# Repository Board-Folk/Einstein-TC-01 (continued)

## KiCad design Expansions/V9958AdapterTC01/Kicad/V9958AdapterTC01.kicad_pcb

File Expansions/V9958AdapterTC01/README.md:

# Einstein TC-01 V9958/V9938 VDP adapter

Adapter board to allow the use of a Yamaha V9958 or V9938 VDP chip on the Tatung Einstein TC-01. The board requires 192KB RAM, as 6 of 4464 (41464) RAM chips, to make the video capability of the board same as (or better than) the Einstein 256, and works with the ROM from that machine, e.g. XTAL MOS 2.1.

The board plugs into the existing VDP socket, replacing the original TMS VDP chip, and connects to video output by replacing the jumpers at M100/101 outputting RGB to the socket on the back of the TC-01. This disconnects the other video circuitry and RF output on the main board, that being YUV based.

The VDP plug to get the right height has been tested with 2 of 20 pin 15mm single pin headers and for connection for video output, 2x08 PC104 pin plug with a single spacer. Careful, as big pins can bork a DIP-40 socket, so be prepared to change that if necessary. Holes for nylon standoffs have been included at the other end of the board for support, though this isn't really necessary.

Address line A1 needs connecting up for this to function as it's not present on the original VDP socket. This is the pin with a box on the two pin header on the edge of this board. The nearest point on the main board for buffered A1 is pin 3 of I28.

Video output is provided by simple transistor based circuits. It seems fine, but some resistor values may need tweaking.

You do not need to fit the video RAM chips on the main board at I40 and I41 with this installed.

Not used or tested at the moment is the other pin on the header next to A1 which is for /WAIT which may or may not be used by any software at all, don't know about this, so connected this with a diode D151 (flagged DNP) between the VDP and the pin header. There isn't anything on the main board that uses /WAIT - that only connects to the Tatung Tube expansion port. This doesn't need connecting unless software uses it, and isn't required to function generally.

Note: The pre-connected solder bridge on the bottom of the board - required for the V9958 - should be cut if installing a V9938. This has now been tested and works fine.

Some fake/relabelled AliExpress RAM got very hot and died on this board after passing regular RAM tests, so be careful what you use. Not sure of the official speed requirements. Equally, there are plenty of completely fake V9958, many labelled copyright 1901.

## Update

A couple of issues have been noted when installing this on an original factory built TC-01 that didn't crop up in testing on the replica build. The first relating to this board, the second relating to the use of the Einstein 256 ROM in the TC-01.

### Fix 1

The original voltage regulator at I106 as factory fitted is a LM350T5, which with this VDP adapter fitted overheats and cuts out causing the system to crash. This needs replacing with a higher rating compatible regulator, 1 Amp or greater. Fitting the wrong voltage regulator or voltage regulator the wrong way round will cause serious damage. This has been successfully tested with a Traco TSR 1-2450. You can test the voltage either side of C057 (C57 on the replica) before fitting any VDP for 5V.

### Fix 2

On some systems with the Einstein 256 ROM fitted, Alph lock randomly enables and disables. This is due to a port being missing at address 26h that is present on the Einstein 256 and not on the TC-01. A patch to the ROM is needed to stop this happening.

Port 26h is read and checked for bit 0 for the Alph key being pressed in 3 places in the ROM code, first offset 7d8h. The three occurrences of db26e601 can be replaced with with db26e600 - removing the bit comparison for the Alph key.

## Photos

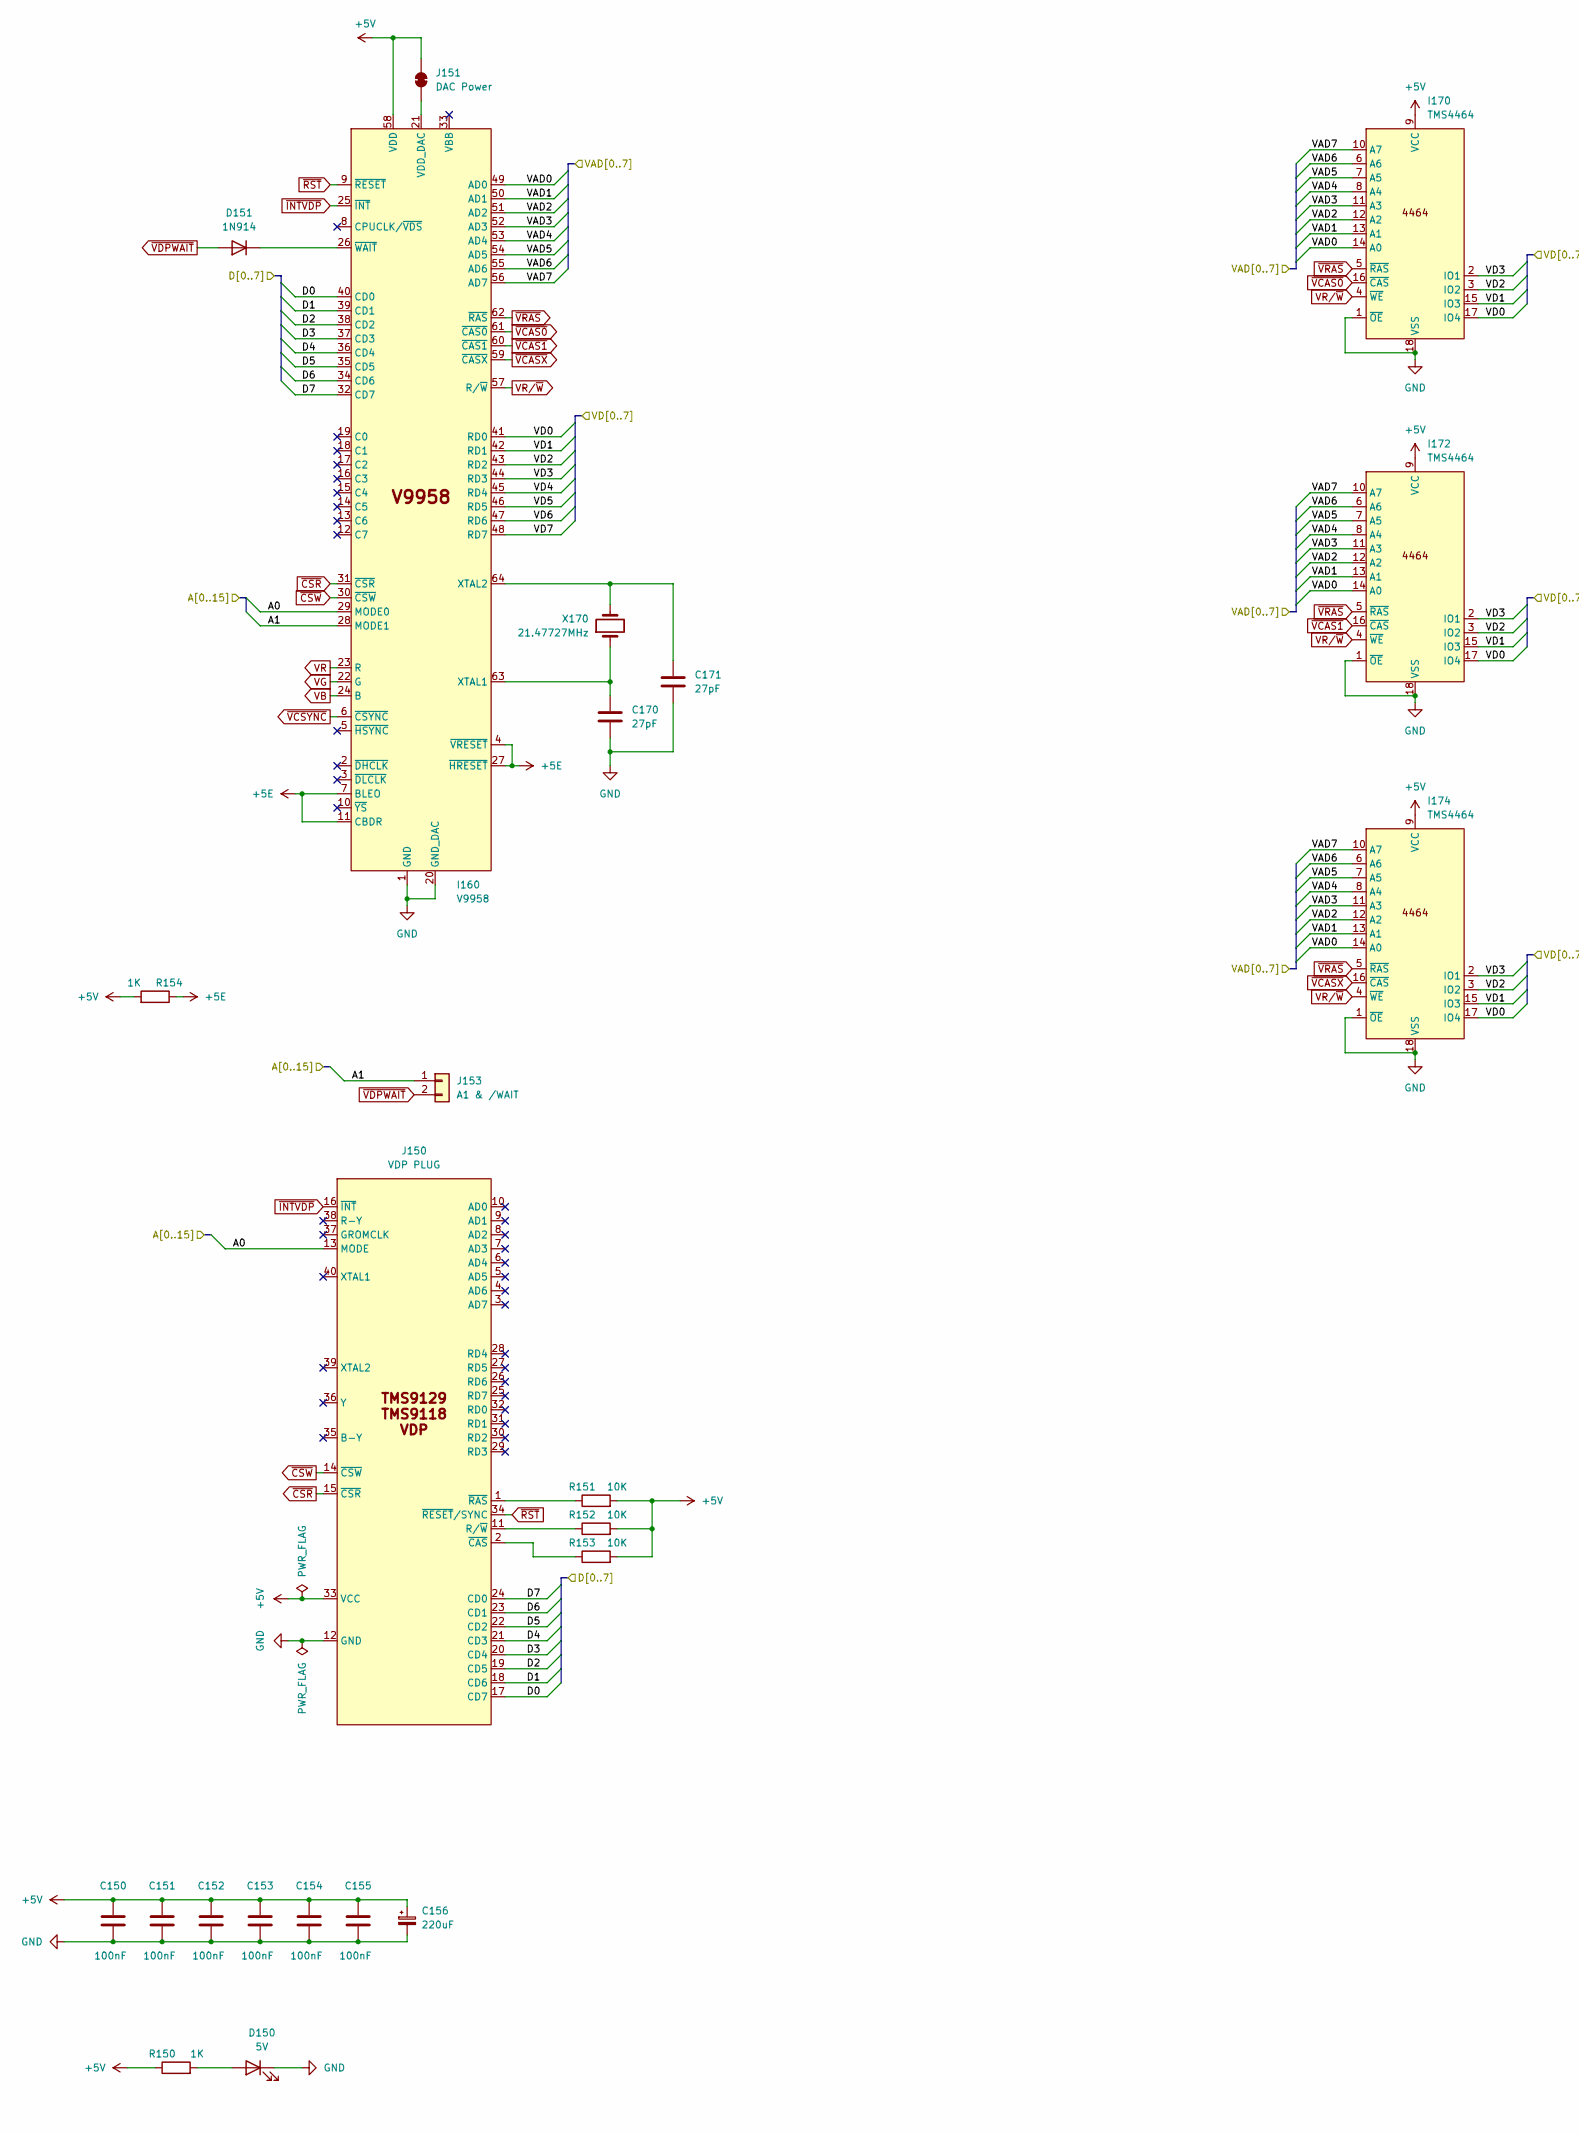
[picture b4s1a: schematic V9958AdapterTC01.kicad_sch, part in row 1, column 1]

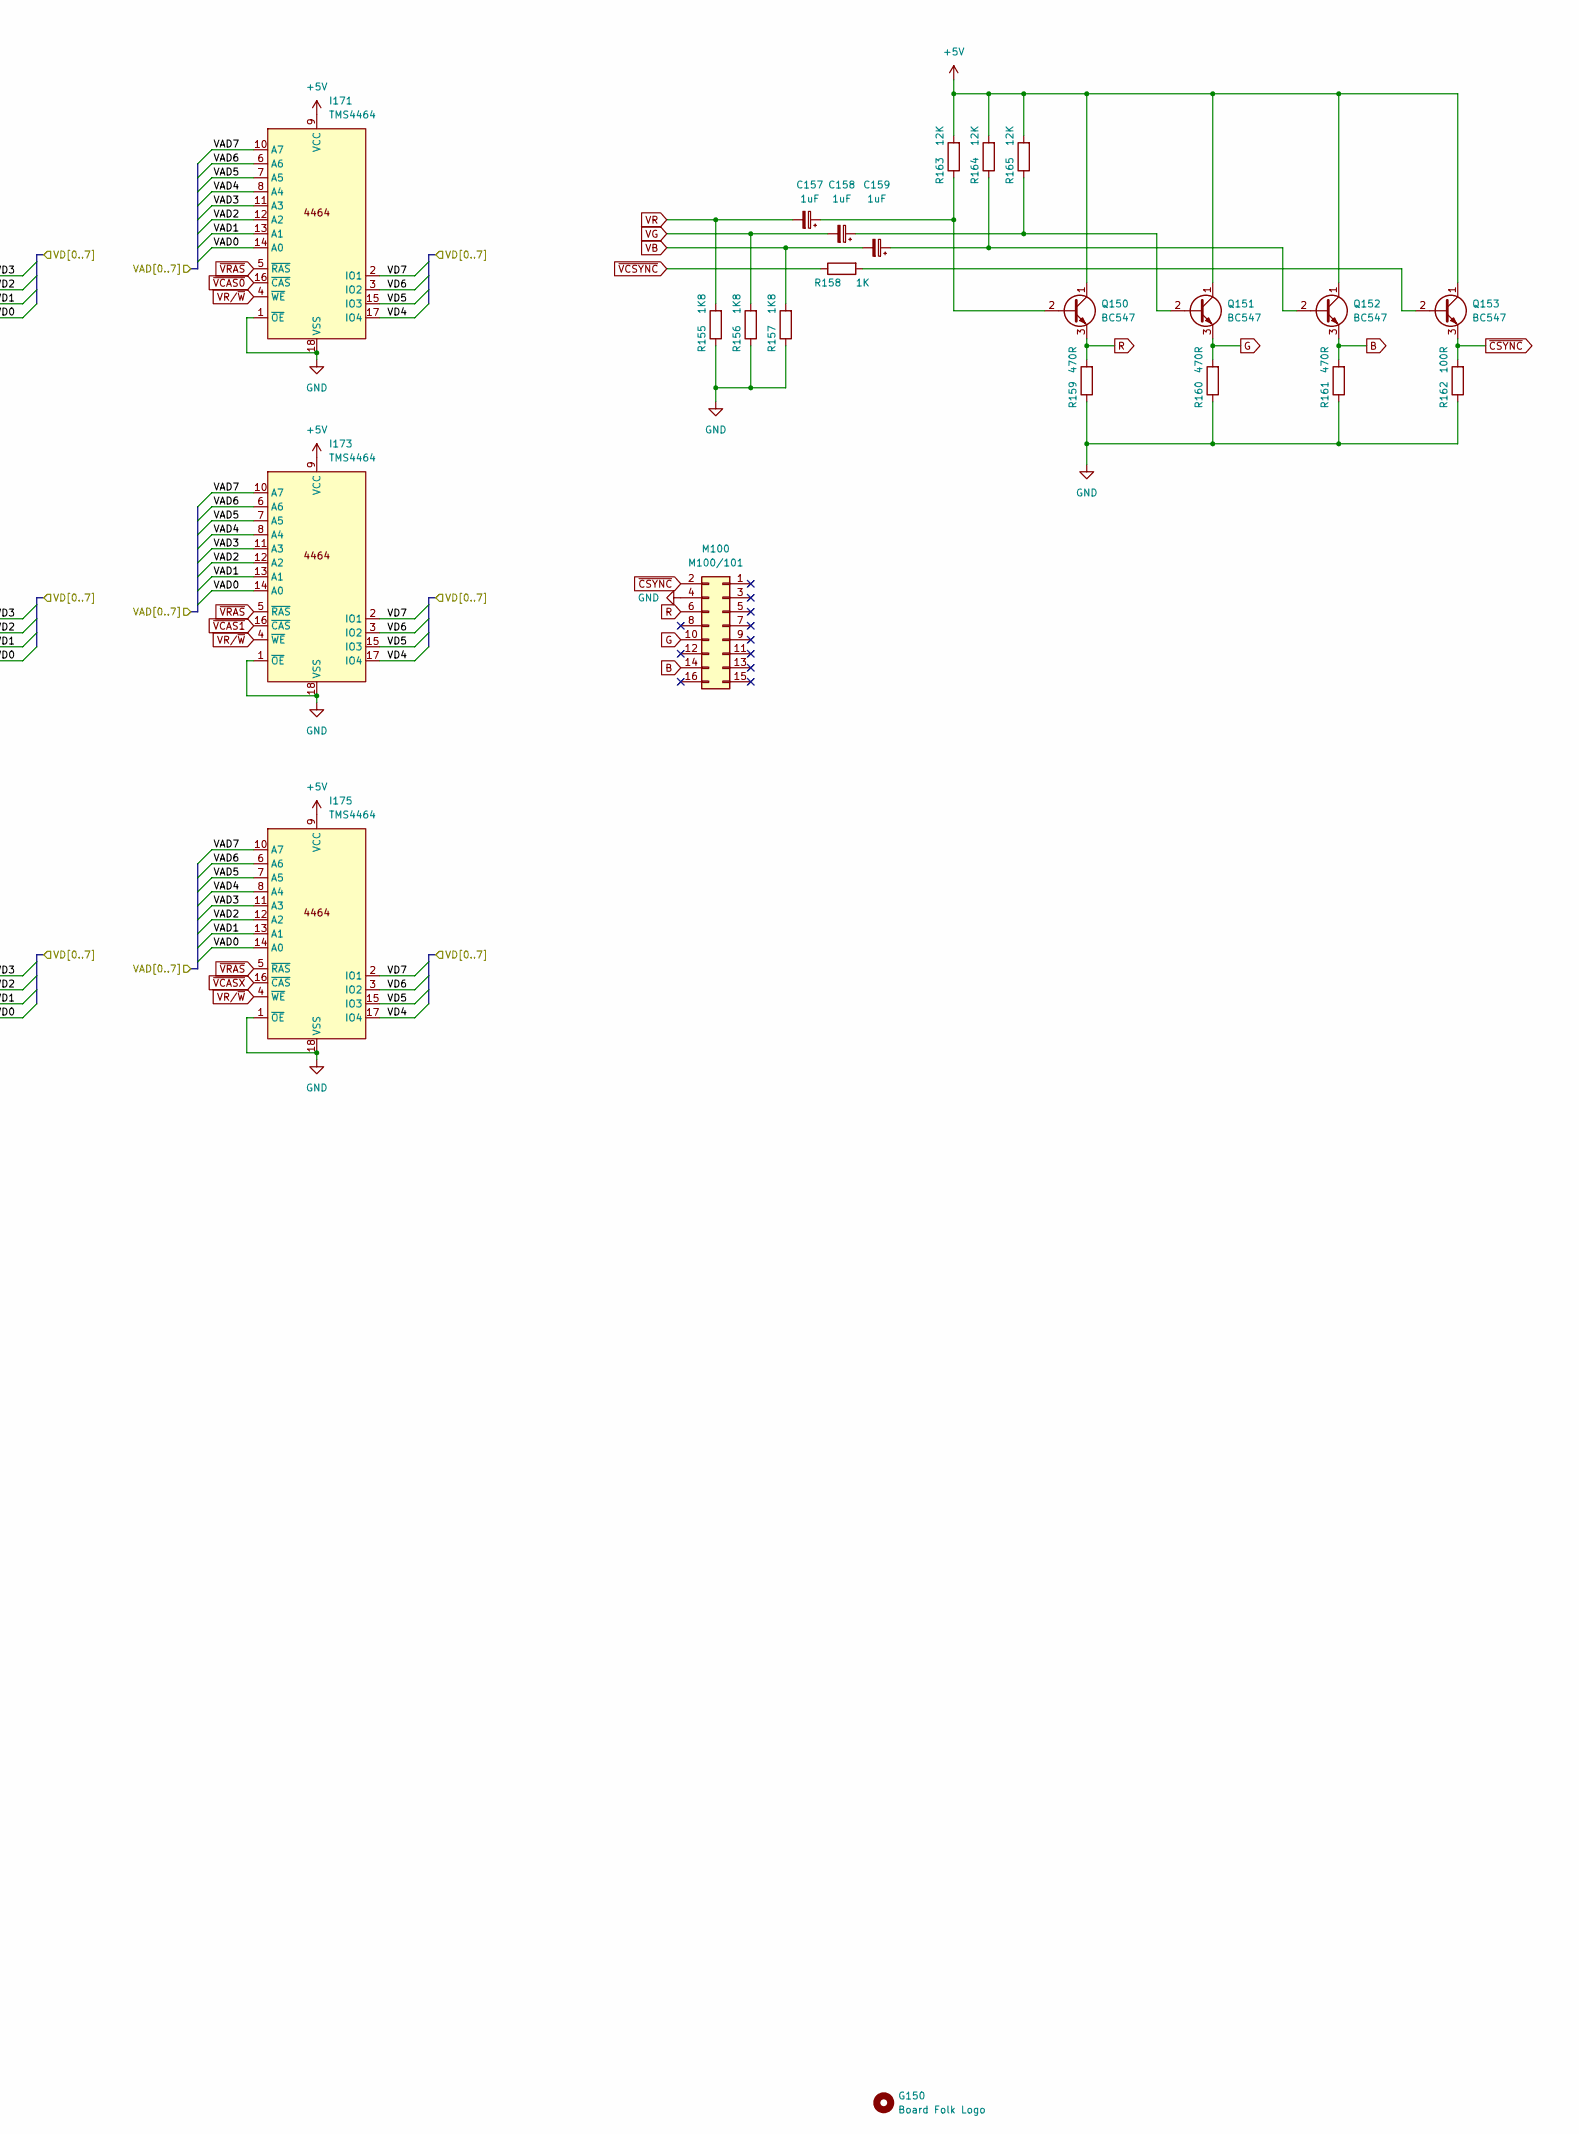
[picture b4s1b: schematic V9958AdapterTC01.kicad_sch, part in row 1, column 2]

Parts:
C150, C151, C152, C153, C154, C155: 100nF; C_Disc_5.08mm
C156: 220uF; Elec_5.08mm - Big Box
C157, C158, C159: 1uF; CP_2.5MM
C170, C171: 27pF; C_Disc_5.08mm
D150: 5V; LED_D3.0mm
D151: 1N914; Diode 7.62mm
G150: Board Folk Logo; BF12
I160: V9958; DIP-64_1.78mm Pitch_Socket
I170, I171, I172, I173, I174, I175: TMS4464; DIP-18_W7.62mm
J150: VDP PLUG; DIP-40_W15.24mm_Plug
J151: DAC Power; SolderJumper-2_P1.3mm_Bridged_RoundedPad1.0x1.5mm
J153: A1 & /WAIT; M11 PinHeader_1x02_P2.54mm
M100: M100/101; PinSocket_2x08_P2.54mm_Vertical
Q150, Q151, Q152, Q153: BC547; Transistor - Box 1 (Leg Rear)
R150, R154, R158: 1K; Resistor 10.16mm
R151, R152, R153: 10K; Resistor 10.16mm
R155, R156, R157: 1K8; Resistor 10.16mm
R159, R160, R161: 470R; Resistor 10.16mm
R162: 100R; Resistor 10.16mm
R163, R164, R165: 12K; Resistor 10.16mm
X170: 21.47727MHz; Crystal

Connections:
+5E: I160.4 (~VRESET), I160.7 (BLEO), I160.11 (CBDR), I160.27 (~HRESET), R154.1
+5V: C150.2, C151.2, C152.2, C153.2, C154.2, C155.2, C156.1, I160.58 (VDD), I170.9 (VCC), I171.9 (VCC), I172.9 (VCC), I173.9 (VCC), I174.9 (VCC), I175.9 (VCC), J150.33 (VCC), J151.2 (B), Q150.1 (C), Q151.1 (C), Q152.1 (C), Q153.1 (C), R150.1, R151.2, R152.2, R153.2, R154.2, R163.2, R164.2, R165.2
/A0: I160.29 (MODE0), J150.13 (MODE)
/A1: I160.28 (MODE1), J153.1
/D0: I160.40 (CD0), J150.17 (CD7)
/D1: I160.39 (CD1), J150.18 (CD6)
/D2: I160.38 (CD2), J150.19 (CD5)
/D3: I160.37 (CD3), J150.20 (CD4)
/D4: I160.36 (CD4), J150.21 (CD3)
/D5: I160.35 (CD5), J150.22 (CD2)
/D6: I160.34 (CD6), J150.23 (CD1)
/D7: I160.32 (CD7), J150.24 (CD0)
/VAD0: I160.49 (AD0), I170.14 (A0), I171.14 (A0), I172.14 (A0), I173.14 (A0), I174.14 (A0), I175.14 (A0)
/VAD1: I160.50 (AD1), I170.13 (A1), I171.13 (A1), I172.13 (A1), I173.13 (A1), I174.13 (A1), I175.13 (A1)
/VAD2: I160.51 (AD2), I170.12 (A2), I171.12 (A2), I172.12 (A2), I173.12 (A2), I174.12 (A2), I175.12 (A2)
/VAD3: I160.52 (AD3), I170.11 (A3), I171.11 (A3), I172.11 (A3), I173.11 (A3), I174.11 (A3), I175.11 (A3)
/VAD4: I160.53 (AD4), I170.8 (A4), I171.8 (A4), I172.8 (A4), I173.8 (A4), I174.8 (A4), I175.8 (A4)
/VAD5: I160.54 (AD5), I170.7 (A5), I171.7 (A5), I172.7 (A5), I173.7 (A5), I174.7 (A5), I175.7 (A5)
/VAD6: I160.55 (AD6), I170.6 (A6), I171.6 (A6), I172.6 (A6), I173.6 (A6), I174.6 (A6), I175.6 (A6)
/VAD7: I160.56 (AD7), I170.10 (A7), I171.10 (A7), I172.10 (A7), I173.10 (A7), I174.10 (A7), I175.10 (A7)
/VD0: I160.41 (RD0), I170.17 (IO4), I172.17 (IO4), I174.17 (IO4)
/VD1: I160.42 (RD1), I170.15 (IO3), I172.15 (IO3), I174.15 (IO3)
/VD2: I160.43 (RD2), I170.3 (IO2), I172.3 (IO2), I174.3 (IO2)
/VD3: I160.44 (RD3), I170.2 (IO1), I172.2 (IO1), I174.2 (IO1)
/VD4: I160.45 (RD4), I171.17 (IO4), I173.17 (IO4), I175.17 (IO4)
/VD5: I160.46 (RD5), I171.15 (IO3), I173.15 (IO3), I175.15 (IO3)
/VD6: I160.47 (RD6), I171.3 (IO2), I173.3 (IO2), I175.3 (IO2)
/VD7: I160.48 (RD7), I171.2 (IO1), I173.2 (IO1), I175.2 (IO1)
B: M100.14, Q152.3 (E), R161.2
G: M100.10, Q151.3 (E), R160.2
GND: C150.1, C151.1, C152.1, C153.1, C154.1, C155.1, C156.2, C170.2, C171.2, D150.1 (K), I160.1 (GND), I160.20 (GND_DAC), I170.1 (~OE), I170.18 (VSS), I171.1 (~OE), I171.18 (VSS), I172.1 (~OE), I172.18 (VSS), I173.1 (~OE), I173.18 (VSS), I174.1 (~OE), I174.18 (VSS), I175.1 (~OE), I175.18 (VSS), J150.12 (GND), M100.4, R155.1, R156.1, R157.1, R159.1, R160.1, R161.1, R162.1
unnamed: D150.2 (A), R150.2
unnamed: D151.1 (K), I160.26 (~WAIT)
unnamed: I160.21 (VDD_DAC), J151.1 (A)
unnamed: C170.1, I160.63 (XTAL1), X170.1
unnamed: C171.1, I160.64 (XTAL2), X170.2
unnamed: J150.11 (R/~W), R152.1
unnamed: J150.2 (~CAS), R153.1
unnamed: J150.1 (~RAS), R151.1
unnamed: C157.1, Q150.2 (B), R163.1
unnamed: C158.1, Q151.2 (B), R165.1
unnamed: C159.1, Q152.2 (B), R164.1
unnamed: Q153.2 (B), R158.2
R: M100.6, Q150.3 (E), R159.2
VB: C159.2, I160.24 (B), R157.2
VG: C158.2, I160.22 (G), R156.2
VR: C157.2, I160.23 (R), R155.2
VR/~W: I160.57 (R/~W), I170.4 (~WE), I171.4 (~WE), I172.4 (~WE), I173.4 (~WE), I174.4 (~WE), I175.4 (~WE)
~CSR: I160.31 (~CSR), J150.15 (~CSR)
~CSW: I160.30 (~CSW), J150.14 (~CSW)
~CSYNC: M100.2, Q153.3 (E), R162.2
~INTVDP: I160.25 (~INT), J150.16 (~INT)
~RST: I160.9 (~RESET), J150.34 (~RESET/SYNC)
~VCAS0: I160.61 (~CAS0), I170.16 (~CAS), I171.16 (~CAS)
~VCAS1: I160.60 (~CAS1), I172.16 (~CAS), I173.16 (~CAS)
~VCASX: I160.59 (~CASX), I174.16 (~CAS), I175.16 (~CAS)
~VCSYNC: I160.6 (~CSYNC), R158.1
~VDPWAIT: D151.2 (A), J153.2
~VRAS: I160.62 (~RAS), I170.5 (~RAS), I171.5 (~RAS), I172.5 (~RAS), I173.5 (~RAS), I174.5 (~RAS), I175.5 (~RAS)

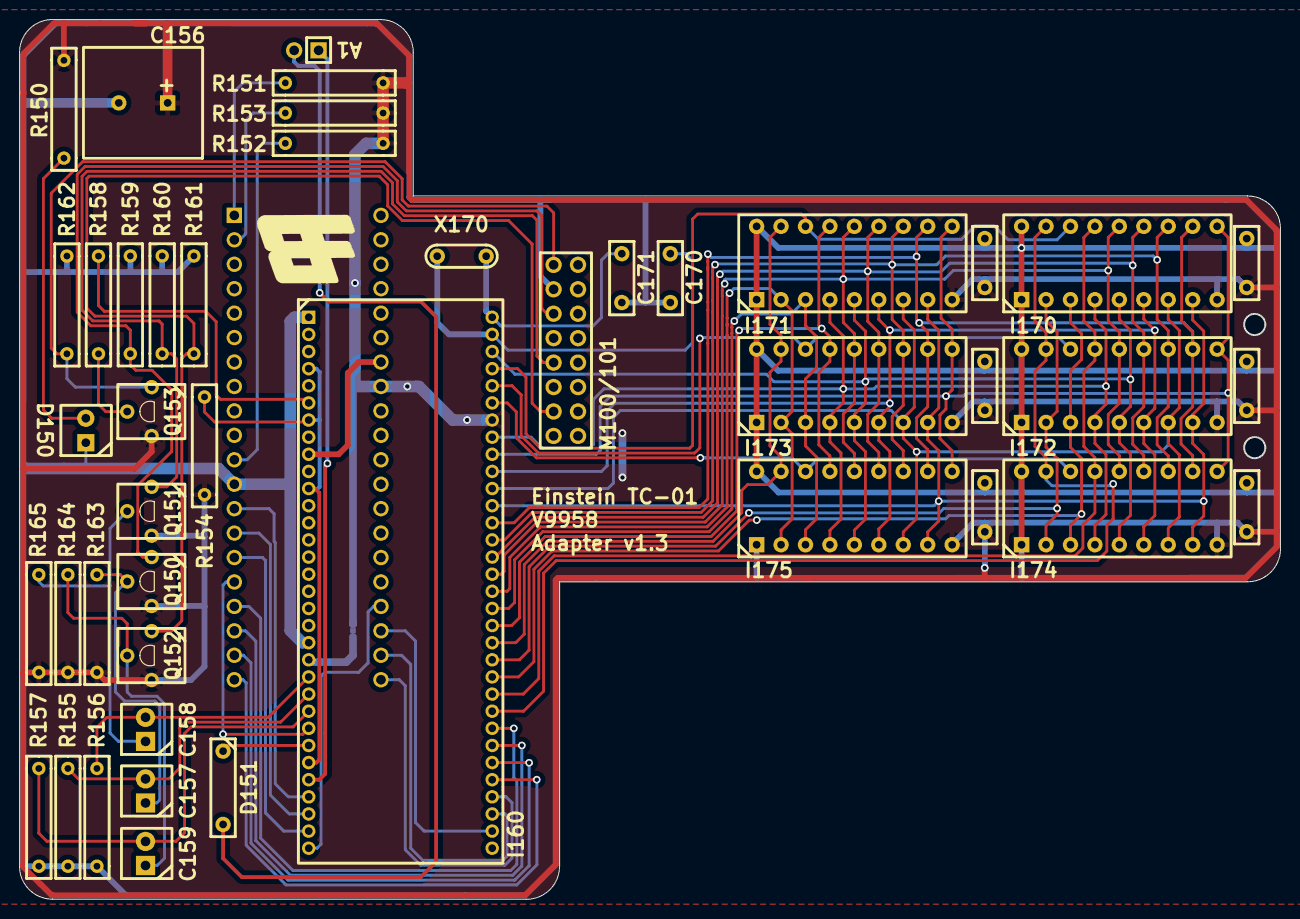
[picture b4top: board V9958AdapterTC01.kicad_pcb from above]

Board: 2 copper layers, 130.9 x 91.3 mm, 47 parts (1 on the bottom side), 59 nets.

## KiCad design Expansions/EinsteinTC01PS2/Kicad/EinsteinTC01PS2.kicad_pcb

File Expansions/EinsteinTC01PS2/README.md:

# EinsteinTC01PS2 v1.2

The Arduino Nano version of a PS/2 keyboard adapter for the Einstein TC-01. This is a larger version of the board intended for development of the Arduino code for it, though is perfectly usable. The board uses separate pins from the Nano to pull Shift, Ctrl and Grph through BC517 darlington pairs.

The board needs a separate 5V power connection as there is no power output on the Einstein's keyboard header. Footprints for both a barrel jack and 2 pin XH connector are provided for this.

There are 3 rows of pin headers, the centre row being 2.54mm, the other 2 2.50mm same as the main board. This arrangement could be use for passthrough to an existing keyboard if necessary.

## Code

The Arduino folder contains the code and can be loaded with Arduino IDE. This is based on C64Keyboard by Robert VanHazinga. Key mappings can be found in keymapping.h. This code is the same for smaller EinsteinTC02PS2, the built binaries for which are in the build folder.

The code is usable as is, but will improve over time. Sometimes gets stuck needing a hard reset. It includes code for future remix versions of the project, including keyboard reset and separate Alph for the 256.

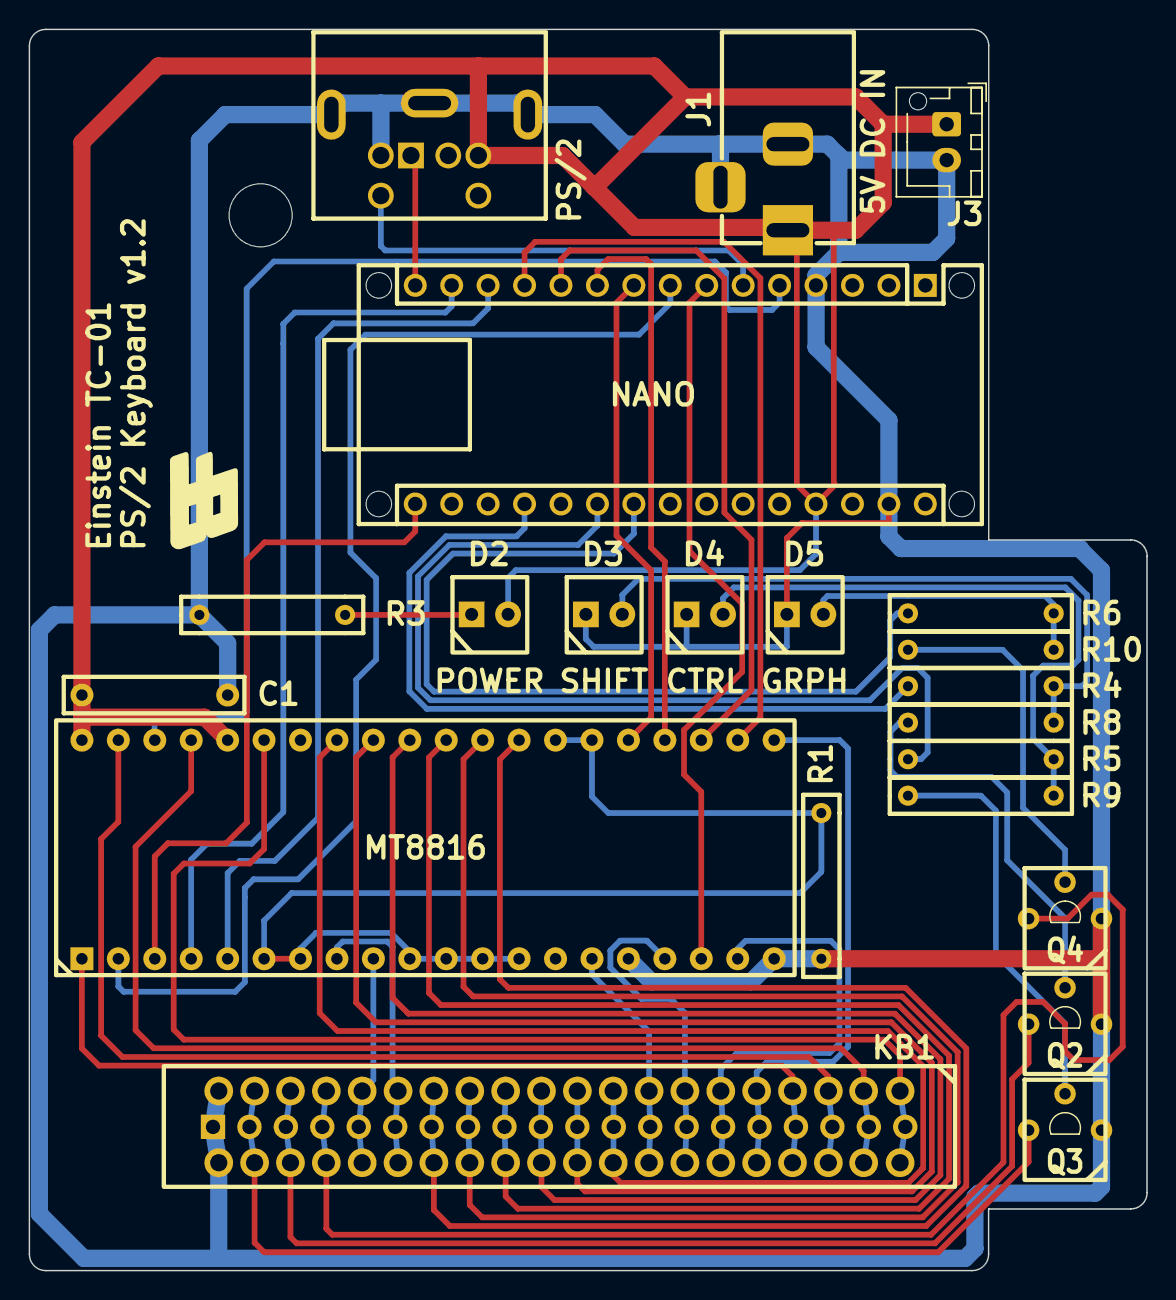
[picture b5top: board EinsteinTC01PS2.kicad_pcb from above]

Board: 2 copper layers, 77.9 x 86.5 mm, 23 parts (0 on the bottom side), 44 nets.

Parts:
C1: 100nF; C_Disc_10.16mm
D2: POWER; LED_D3.0mm
D3: SHIFT; LED_D3.0mm
D4: CTRL; LED_D3.0mm
D5: GRPH; LED_D3.0mm
G1: Board Folk Logo; BF8
J1: 5V DC IN; BarrelJack_Horizontal
J2: PS/2; Connector_Mini-DIN_Female_6Pin_2rows
J3: 5V DC IN; JST_XH_B2B-XH-AM_1x02_P2.50mm_Vertical
KB1: COMPUTER INTERFACE; Keyboard_Triple
Q2, Q3, Q4: BC517; Transistor - Box 1 (Leg Rear)
R1: 10K; Resistor 10.16mm
R3, R8, R9, R10: 1K; Resistor 10.16mm
R4, R5, R6: 470R; Resistor 10.16mm
U1: MT8816; DIP-40_W15.24mm
U2: NANO; Arduino_Nano_WithMountingHoles

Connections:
+5V: C1.1, D2.2 (A), J1.1, J2.4, J3.1, U1.36 (CS), U1.40 (VDD), U2.27 (5V)
AX0: U1.5 (AX0), U2.13 (D10)
AX1: U1.22 (AX1), U2.12 (D9)
AX2: U1.23 (AX2), U2.11 (D8)
AX3: U1.4 (AX3), U2.14 (D11)
AY0: U1.24 (AY0), U2.10 (D7)
AY1: U1.25 (AY1), U2.9 (D6)
AY2: U1.2 (AY2), U2.8 (D5)
CTRL: R5.2, U2.21 (A2)
GND: C1.2, D3.1 (K), D4.1 (K), D5.1 (K), J1.2, J1.3, J2.3, J2.7 (GND), J3.2, KB1.1, Q2.3 (E), Q3.3 (E), Q4.3 (E), R1.2, R3.2, U1.16 (VSS), U1.20 (VEE), U2.4 (GND), U2.29 (GND)
GRPH: R6.2, U2.22 (A3)
MTDATA: U1.38 (DATA), U2.5 (D2)
MTRESET: U1.3 (RESET), U2.16 (D13)
MTSTROBE: U1.18 (STROBE), U2.7 (D4)
unnamed: D2.1 (K), R3.1
unnamed: D3.2 (A), R4.1, R8.1
unnamed: D4.2 (A), R5.1, R9.1
unnamed: D5.2 (A), R6.1, R10.1
unnamed: Q2.2 (B), R8.2
unnamed: Q3.2 (B), R9.2
unnamed: Q4.2 (B), R10.2
unnamed: R1.1, U1.6 (X14), U1.7 (X15), U1.10 (X8), U1.11 (X9), U1.12 (X10), U1.13 (X11), U1.26 (X13), U1.27 (X12)
PS2-CLK: J2.5, U2.6 (D3)
PS2-DATA: J2.1, U2.15 (D12)
SHIFT: R4.2, U2.19 (A0)
X0: KB1.12, U1.33 (X0)
X1: KB1.11, U1.32 (X1)
X2: KB1.10, U1.31 (X2)
X3: KB1.9, U1.30 (X3)
X4: KB1.8, U1.29 (X4)
X5: KB1.7, U1.28 (X5)
X6: KB1.6, U1.8 (X6)
X7: KB1.5, U1.9 (X7)
Y0: KB1.20, U1.35 (Y0)
Y1: KB1.19, U1.37 (Y1)
Y2: KB1.18, U1.39 (Y2)
Y3: KB1.17, U1.1 (Y3)
Y4: KB1.16, U1.21 (Y4)
Y5: KB1.15, U1.19 (Y5)
Y6: KB1.14, U1.17 (Y6)
Y7: KB1.13, U1.15 (Y7)
~CTRL: KB1.2, Q3.1 (C)
~GRPH: KB1.4, Q4.1 (C)
~SHIFT: KB1.3, Q2.1 (C)

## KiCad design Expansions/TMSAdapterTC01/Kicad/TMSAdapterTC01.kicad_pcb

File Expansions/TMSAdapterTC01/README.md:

# Einstein TC-01 TMS9929 adapter

Adapter board to allow the use of a TMS9929 chip on the Tatung Einstein TC-01. The TMS9929 is easier to find than the original VDP, but requires a different type of RAM which needs fitting to the adapter.

Intended to work with 5V 1x16K DRAM chips, e.g. MB8118 or compatible, but can accept 4164 and 41256 RAM, which although is a waste as the majority of the RAM isn't used are more easily and cheaply obtained. This will not work with 4116 RAM as the board doesn't provide the correct voltages.

You do not need to fit the video RAM chips on the main board at I40 and I41 with this installed.

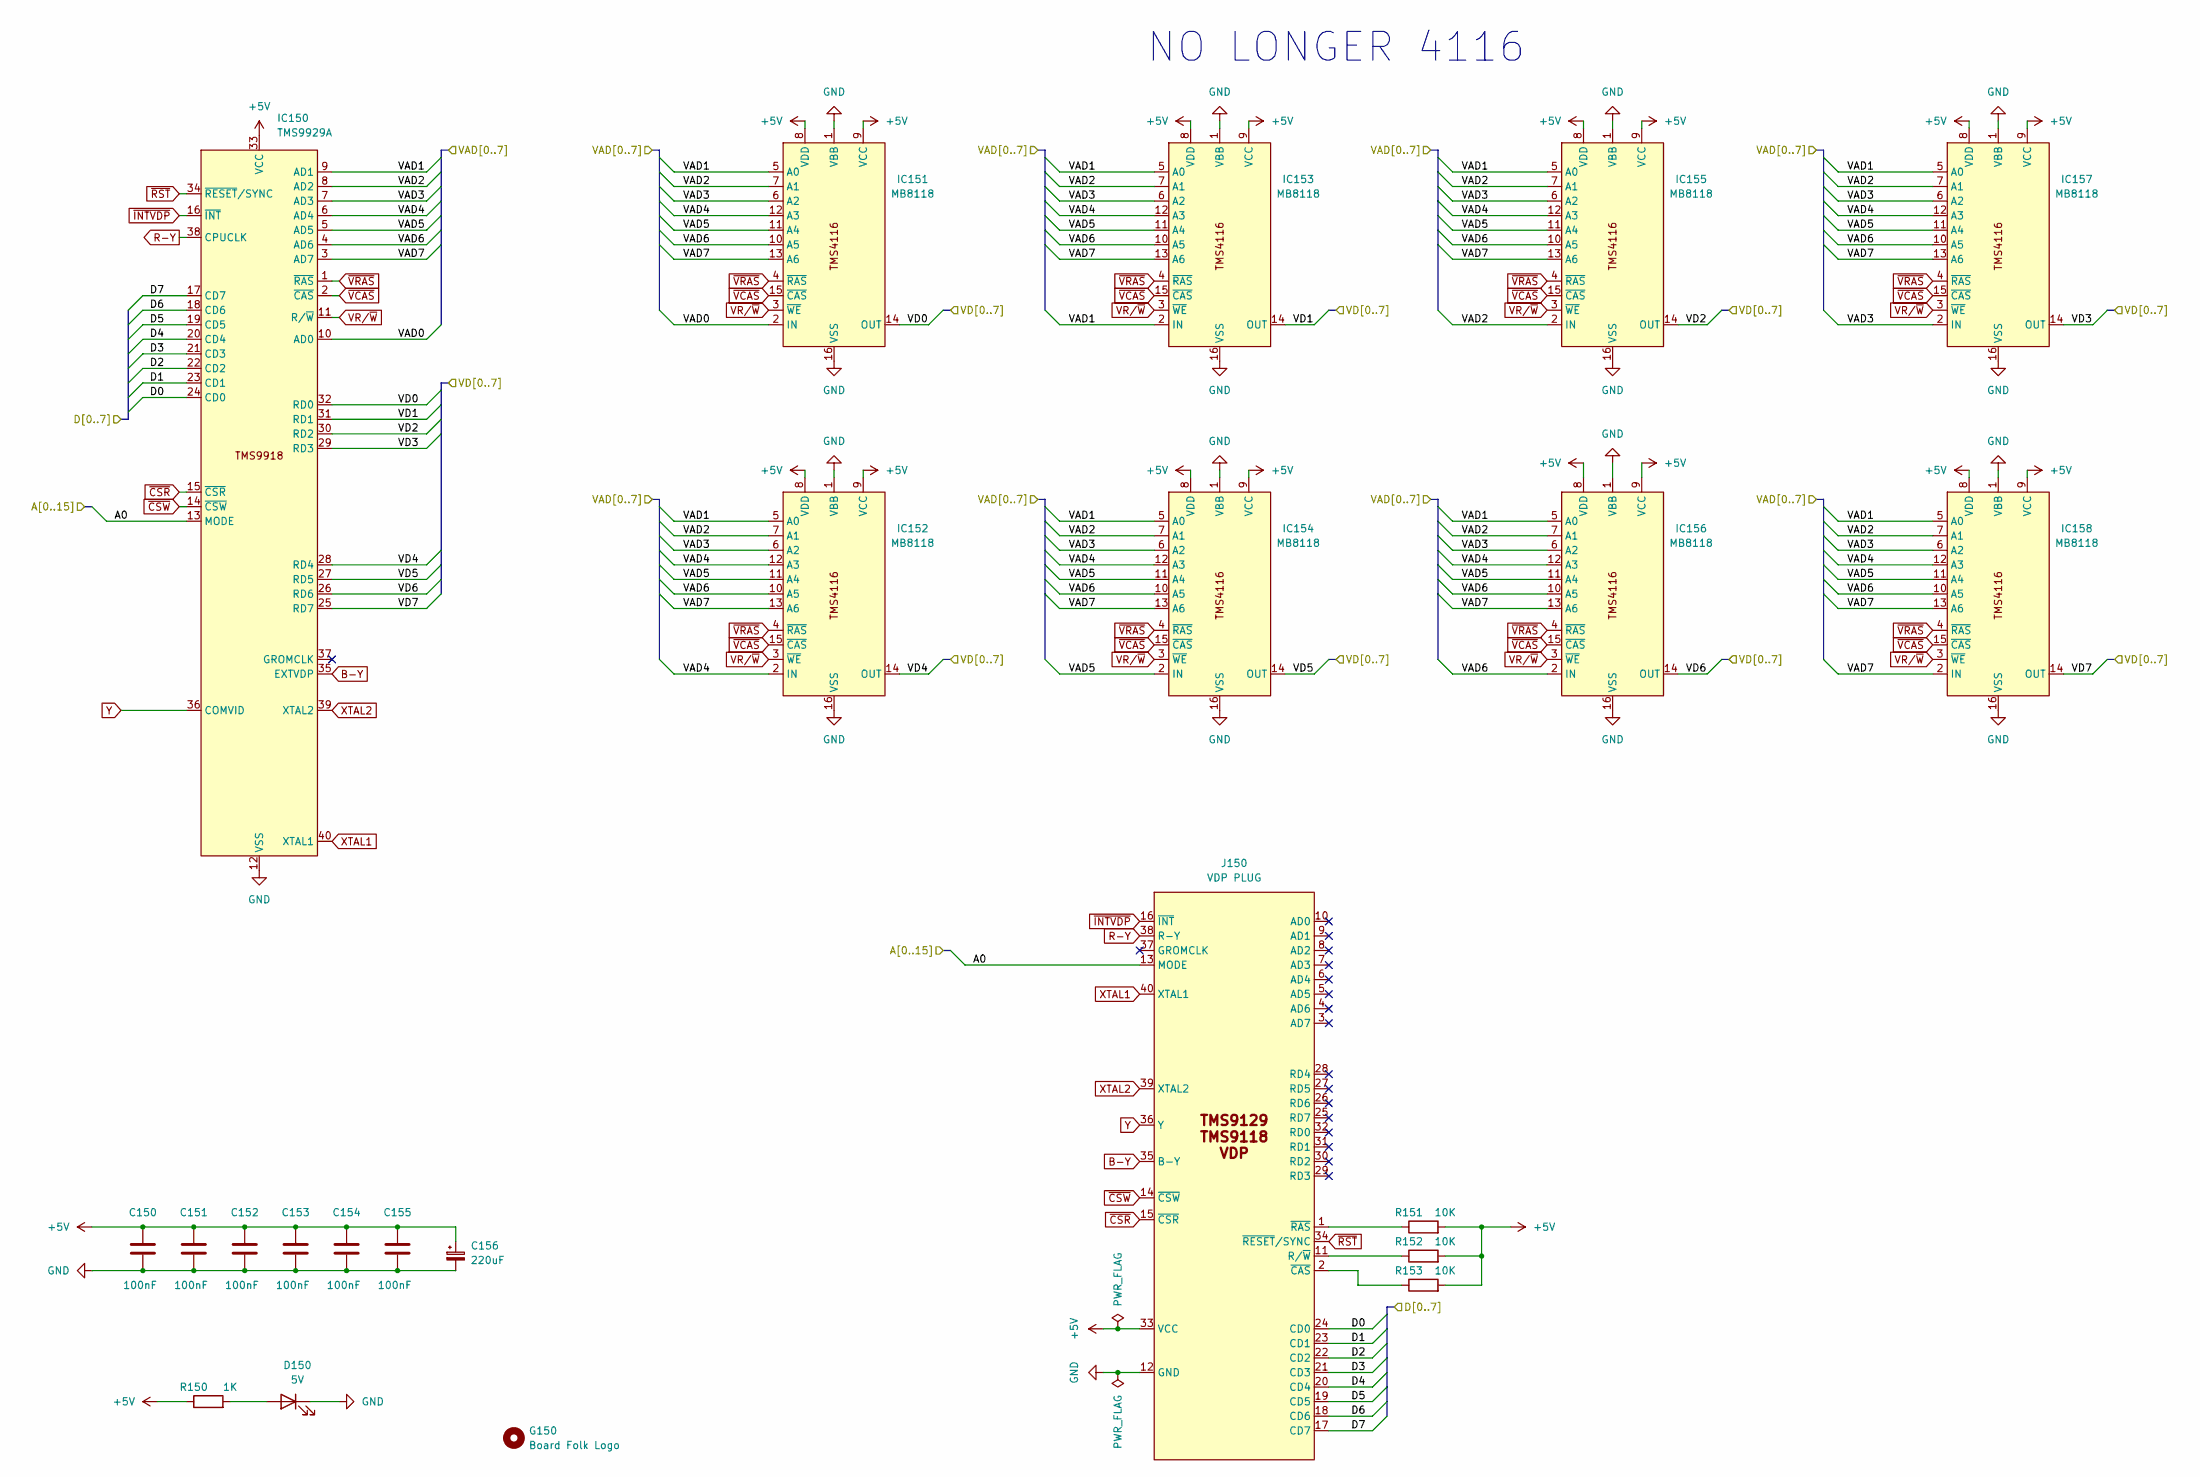
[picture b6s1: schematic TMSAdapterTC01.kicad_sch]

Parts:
C150, C151, C152, C153, C154, C155: 100nF; C_Disc_5.08mm
C156: 220uF; Elec_5.08mm - Big Box
D150: 5V; LED_D3.0mm
G150: Board Folk Logo; BF12
IC150: TMS9929A; DIP-40_W15.24mm
IC151, IC152, IC153, IC154, IC155, IC156, IC157, IC158: MB8118; DIP-16_W7.62mm
J150: VDP PLUG; DIP-40_W15.24mm_Plug
R150: 1K; Resistor 10.16mm
R151, R152, R153: 10K; Resistor 10.16mm

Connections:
+5V: C150.2, C151.2, C152.2, C153.2, C154.2, C155.2, C156.1, IC150.33 (VCC), IC151.8 (VDD), IC151.9 (VCC), IC152.8 (VDD), IC152.9 (VCC), IC153.8 (VDD), IC153.9 (VCC), IC154.8 (VDD), IC154.9 (VCC), IC155.8 (VDD), IC155.9 (VCC), IC156.8 (VDD), IC156.9 (VCC), IC157.8 (VDD), IC157.9 (VCC), IC158.8 (VDD), IC158.9 (VCC), J150.33 (VCC), R150.1, R151.2, R152.2, R153.2
/A0: IC150.13 (MODE), J150.13 (MODE)
/D0: IC150.24 (CD0), J150.24 (CD0)
/D1: IC150.23 (CD1), J150.23 (CD1)
/D2: IC150.22 (CD2), J150.22 (CD2)
/D3: IC150.21 (CD3), J150.21 (CD3)
/D4: IC150.20 (CD4), J150.20 (CD4)
/D5: IC150.19 (CD5), J150.19 (CD5)
/D6: IC150.18 (CD6), J150.18 (CD6)
/D7: IC150.17 (CD7), J150.17 (CD7)
/VAD0: IC150.10 (AD0), IC151.2 (IN)
/VAD1: IC150.9 (AD1), IC151.5 (A0), IC152.5 (A0), IC153.2 (IN), IC153.5 (A0), IC154.5 (A0), IC155.5 (A0), IC156.5 (A0), IC157.5 (A0), IC158.5 (A0)
/VAD2: IC150.8 (AD2), IC151.7 (A1), IC152.7 (A1), IC153.7 (A1), IC154.7 (A1), IC155.2 (IN), IC155.7 (A1), IC156.7 (A1), IC157.7 (A1), IC158.7 (A1)
/VAD3: IC150.7 (AD3), IC151.6 (A2), IC152.6 (A2), IC153.6 (A2), IC154.6 (A2), IC155.6 (A2), IC156.6 (A2), IC157.2 (IN), IC157.6 (A2), IC158.6 (A2)
/VAD4: IC150.6 (AD4), IC151.12 (A3), IC152.2 (IN), IC152.12 (A3), IC153.12 (A3), IC154.12 (A3), IC155.12 (A3), IC156.12 (A3), IC157.12 (A3), IC158.12 (A3)
/VAD5: IC150.5 (AD5), IC151.11 (A4), IC152.11 (A4), IC153.11 (A4), IC154.2 (IN), IC154.11 (A4), IC155.11 (A4), IC156.11 (A4), IC157.11 (A4), IC158.11 (A4)
/VAD6: IC150.4 (AD6), IC151.10 (A5), IC152.10 (A5), IC153.10 (A5), IC154.10 (A5), IC155.10 (A5), IC156.2 (IN), IC156.10 (A5), IC157.10 (A5), IC158.10 (A5)
/VAD7: IC150.3 (AD7), IC151.13 (A6), IC152.13 (A6), IC153.13 (A6), IC154.13 (A6), IC155.13 (A6), IC156.13 (A6), IC157.13 (A6), IC158.2 (IN), IC158.13 (A6)
/VD0: IC150.32 (RD0), IC151.14 (OUT)
/VD1: IC150.31 (RD1), IC153.14 (OUT)
/VD2: IC150.30 (RD2), IC155.14 (OUT)
/VD3: IC150.29 (RD3), IC157.14 (OUT)
/VD4: IC150.28 (RD4), IC152.14 (OUT)
/VD5: IC150.27 (RD5), IC154.14 (OUT)
/VD6: IC150.26 (RD6), IC156.14 (OUT)
/VD7: IC150.25 (RD7), IC158.14 (OUT)
B-Y: IC150.35 (EXTVDP), J150.35 (B-Y)
GND: C150.1, C151.1, C152.1, C153.1, C154.1, C155.1, C156.2, D150.1 (K), IC150.12 (VSS), IC151.1 (VBB), IC151.16 (VSS), IC152.1 (VBB), IC152.16 (VSS), IC153.1 (VBB), IC153.16 (VSS), IC154.1 (VBB), IC154.16 (VSS), IC155.1 (VBB), IC155.16 (VSS), IC156.1 (VBB), IC156.16 (VSS), IC157.1 (VBB), IC157.16 (VSS), IC158.1 (VBB), IC158.16 (VSS), J150.12 (GND)
unnamed: D150.2 (A), R150.2
unnamed: J150.11 (R/~W), R152.1
unnamed: J150.2 (~CAS), R153.1
unnamed: J150.1 (~RAS), R151.1
R-Y: IC150.38 (CPUCLK), J150.38 (R-Y)
VR/~W: IC150.11 (R/~W), IC151.3 (~WE), IC152.3 (~WE), IC153.3 (~WE), IC154.3 (~WE), IC155.3 (~WE), IC156.3 (~WE), IC157.3 (~WE), IC158.3 (~WE)
XTAL1: IC150.40 (XTAL1), J150.40 (XTAL1)
XTAL2: IC150.39 (XTAL2), J150.39 (XTAL2)
Y: IC150.36 (COMVID), J150.36 (Y)
~CSR: IC150.15 (~CSR), J150.15 (~CSR)
~CSW: IC150.14 (~CSW), J150.14 (~CSW)
~INTVDP: IC150.16 (~INT), J150.16 (~INT)
~RST: IC150.34 (~RESET/SYNC), J150.34 (~RESET/SYNC)
~VCAS: IC150.2 (~CAS), IC151.15 (~CAS), IC152.15 (~CAS), IC153.15 (~CAS), IC154.15 (~CAS), IC155.15 (~CAS), IC156.15 (~CAS), IC157.15 (~CAS), IC158.15 (~CAS)
~VRAS: IC150.1 (~RAS), IC151.4 (~RAS), IC152.4 (~RAS), IC153.4 (~RAS), IC154.4 (~RAS), IC155.4 (~RAS), IC156.4 (~RAS), IC157.4 (~RAS), IC158.4 (~RAS)

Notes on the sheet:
NO LONGER 4116

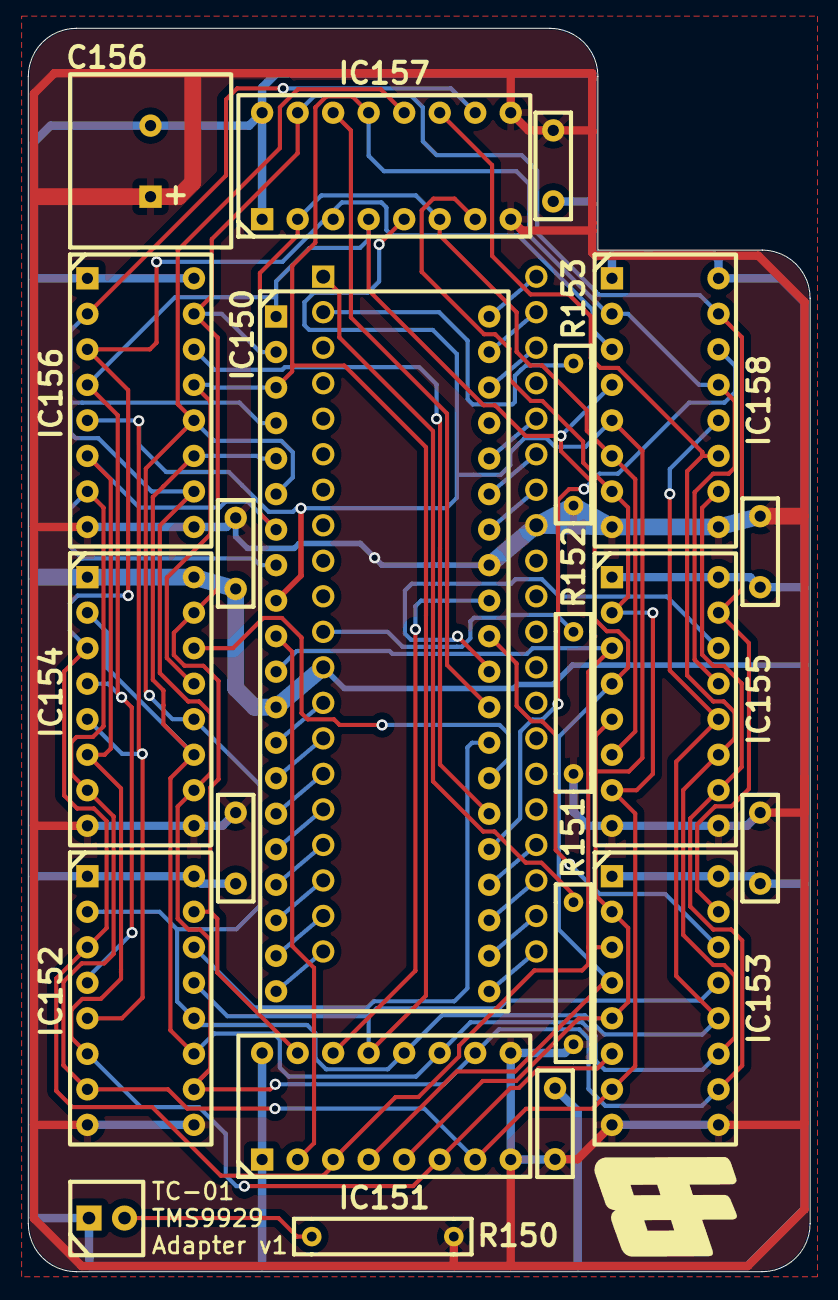
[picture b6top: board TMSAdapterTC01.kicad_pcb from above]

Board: 2 copper layers, 55.9 x 88.9 mm, 23 parts (0 on the bottom side), 43 nets.

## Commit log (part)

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2025-11-02 v1.1
2025-11-13 TMS9929 Adapter
2025-12-06 Images of PS/2 boards
2025-12-06 PS/2 Boards and Code
2025-12-06 Update PS/2 Readmes
2025-12-16 v1.1 Additional Footprints and Symbols update only
2025-12-16 V9958 v1.3 Adapter
2025-12-28 TC-02 Mini v1
2026-01-25 Einstein CE v1.1
2026-02-03 PS/2 v0.3
2026-03-14 v1.1 Project Update
2026-03-14 TC01 Tandy Joystick Adapter
2026-03-15 Atari Joystick Interface
2026-03-16 Wrong Directions!
2026-03-23 Atari Joystick Adapter v1.1
